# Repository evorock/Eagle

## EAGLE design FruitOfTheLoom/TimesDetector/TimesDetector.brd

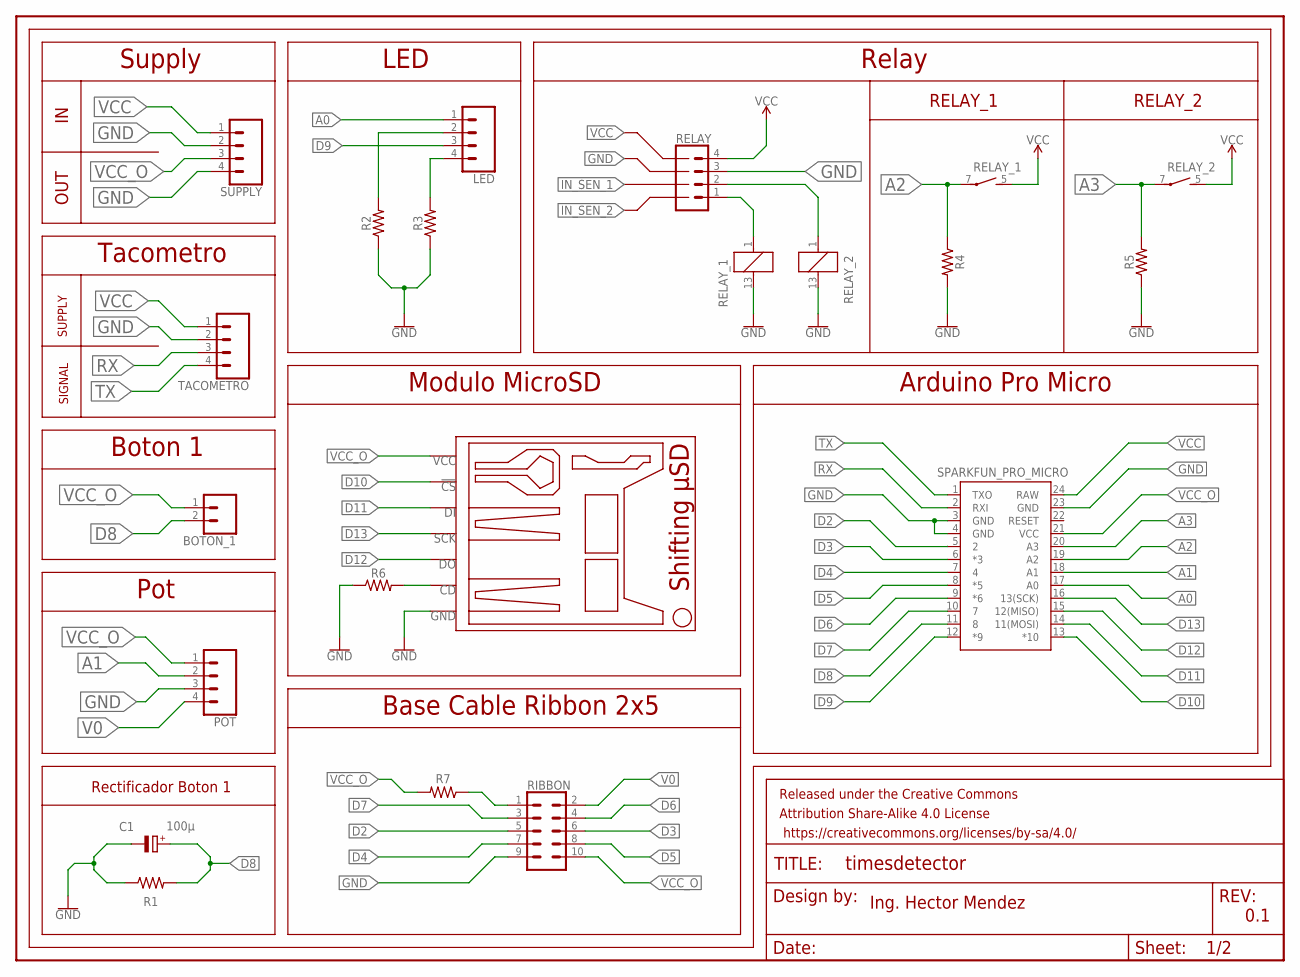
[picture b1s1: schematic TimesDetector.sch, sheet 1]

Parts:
B1: SPARKFUN_PRO_MICRO
BOTON_1: CONN_025MM; SCREWTERMINAL-5MM-2
C1: 100µ; E2,5-6E
FRAME1: FRAME-LETTER; CREATIVE_COMMONS
LED: CONN_04SCREW_LOCK; SCREWTERMINAL-3.5MM-4_LOCK
MODULE1: MICROSD_SPARKFUN_LEVEL_SHIFTING_MODULE; MICROSD_SPARKFUN_LEVEL_SHFTING_MODULE
POT: CONN_04SCREW_LOCK; SCREWTERMINAL-3.5MM-4_LOCK
R1, R2, R3, R4, R5, R6, R7: AXIAL-0.3
RELAY: CONN_04SCREW_LOCK; SCREWTERMINAL-3.5MM-4_LOCK
RELAY_1, RELAY_2: G6D-1A-ASI12VDC; G6D
RIBBON: CONN_05X2SHD; 2X5-SHROUDED
SUPPLY: CONN_04SCREW_LOCK; SCREWTERMINAL-3.5MM-4_LOCK
TACOMETRO: CONN_04SCREW_LOCK; SCREWTERMINAL-3.5MM-4_LOCK

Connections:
A0: B1.17 (A0), LED.1
A1: B1.18 (A1), POT.2
A2: B1.19 (A2), R4.P$1 (1), RELAY_1.7
A3: B1.20 (A3), R5.P$2 (2), RELAY_2.7
D2: B1.5 (2), RIBBON.5; also elsewhere on the board
D3: B1.6 (*3), RIBBON.6; also elsewhere on the board
D4: B1.7 (4), RIBBON.7
D5: B1.8 (*5), RIBBON.8; also elsewhere on the board
D6: B1.9 (*6), RIBBON.4; also elsewhere on the board
D7: B1.10 (7), RIBBON.3
D8: B1.11 (8), BOTON_1.2, C1.+, R1.P$2 (2)
D9: B1.12 (*9), LED.3; also elsewhere on the board
D10: B1.13 (*10), MODULE1.P_!CS
D11: B1.14 (11(MOSI)), MODULE1.P_DI
D12: B1.15 (12(MISO)), MODULE1.P_DO
D13: B1.16 (13(SCK)), MODULE1.P_SCK
GND: B1.3 (GND), B1.4 (GND), B1.23 (GND), C1.-, MODULE1.P_GND (GND), POT.3, R1.P$1 (1), R2.P$1 (1), R3.P$1 (1), R4.P$2 (2), R5.P$1 (1), R6.P$1 (1), RELAY.3, RELAY_1.13 (2), RELAY_2.13 (2), RIBBON.9, SUPPLY.2, SUPPLY.4, TACOMETRO.2
IN_SEN_1: RELAY.2, RELAY_2.1
IN_SEN_2: RELAY.1, RELAY_1.1
unnamed: MODULE1.P_CD, R6.P$2 (2)
unnamed: LED.4, R3.P$2 (2)
unnamed: LED.2, R2.P$2 (2)
unnamed: R7.P$1 (1), RIBBON.1
RX: B1.2 (RXI), TACOMETRO.3
TX: B1.1 (TXO), TACOMETRO.4
V0: POT.4, RIBBON.2
VCC: B1.24 (RAW), RELAY.4, RELAY_1.5 (S), RELAY_2.5 (S), SUPPLY.1, TACOMETRO.1
VCC_O: B1.21 (VCC), BOTON_1.1, MODULE1.P_VCC, POT.1, R7.P$2 (2), RIBBON.10, SUPPLY.3

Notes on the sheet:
Supply
Tacometro
Boton 1
Pot
LED
OUT
SIGNAL
SUPPLY
Rectificador Boton 1
Relay
Modulo MicroSD
Arduino Pro Micro
Base Cable Ribbon 2x5
Ing. Hector Mendez
0.1
RELAY_1
RELAY_2

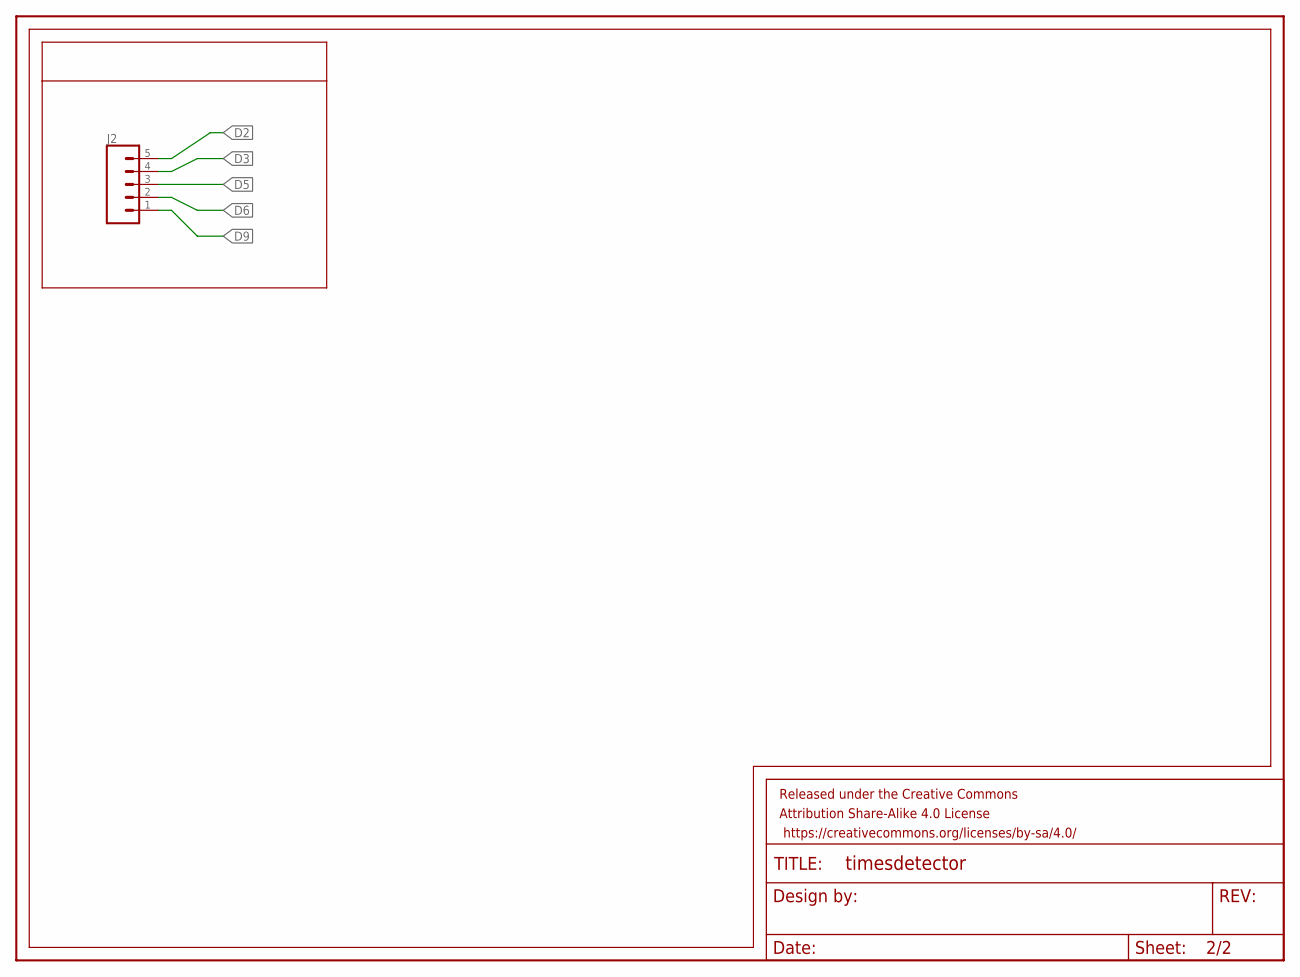
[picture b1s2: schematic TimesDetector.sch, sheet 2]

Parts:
FRAME3: FRAME-LETTERNO_PACKAGE; DUMMY
J2: CONN_05PTH_LONGPADS; 1X05_LONGPADS

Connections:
D2: J2.5; also elsewhere on the board
D3: J2.4; also elsewhere on the board
D5: J2.3; also elsewhere on the board
D6: J2.2; also elsewhere on the board
D9: J2.1; also elsewhere on the board

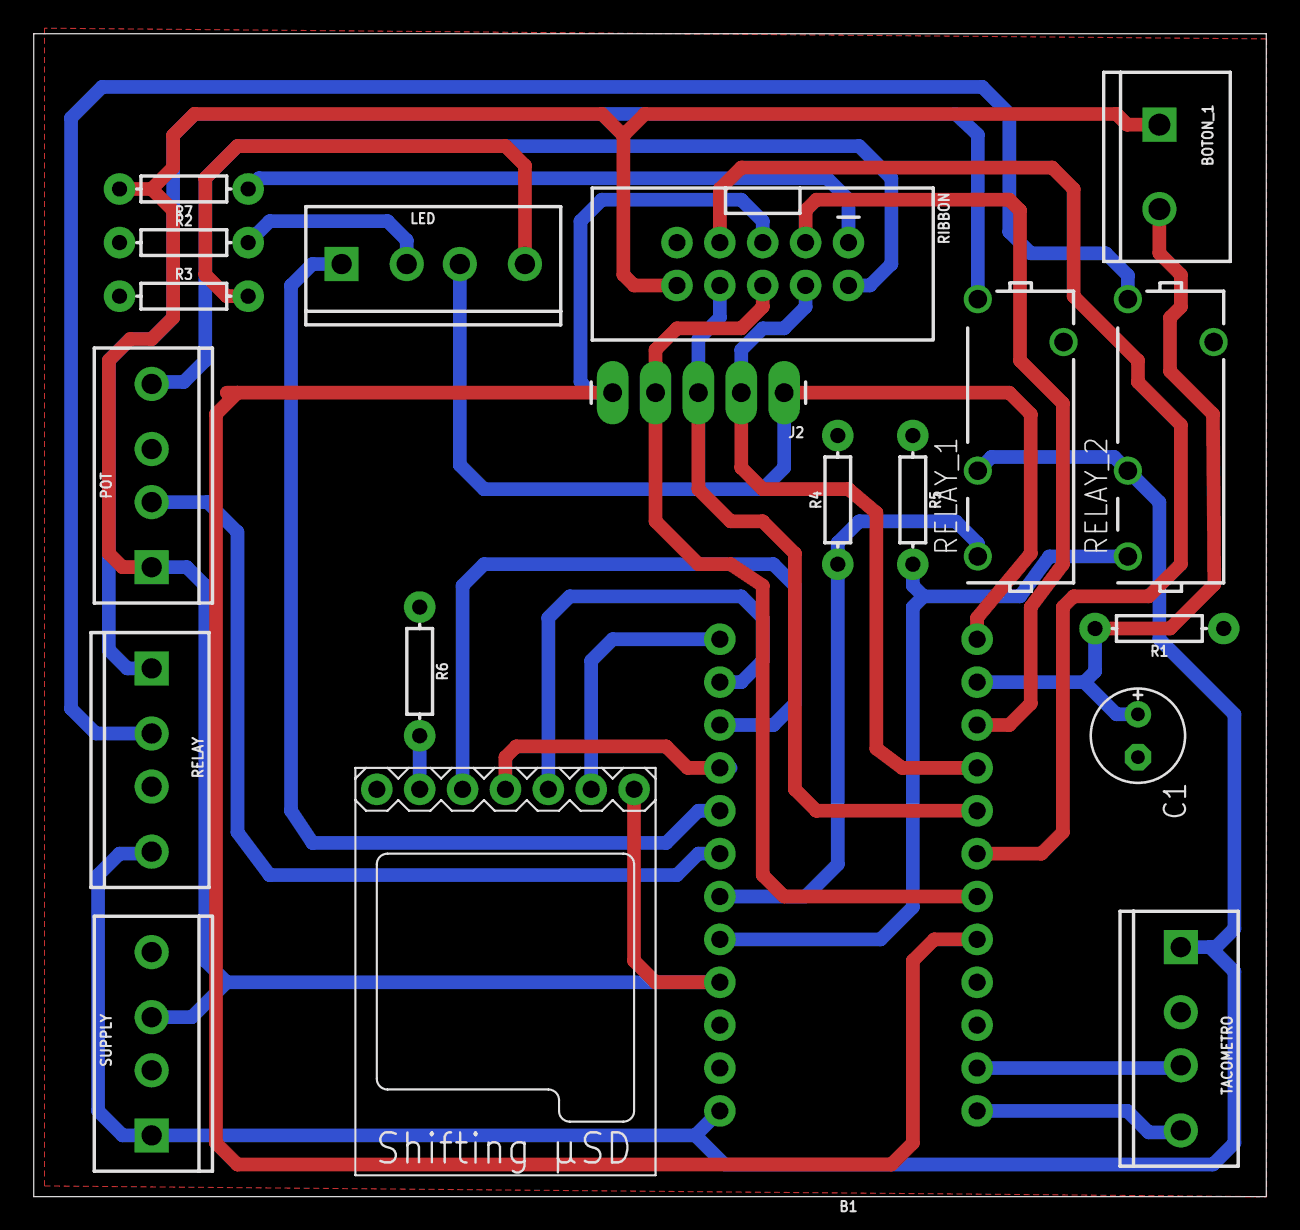
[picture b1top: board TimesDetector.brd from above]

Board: 2 copper layers, 73.0 x 68.9 mm, 22 parts (0 on the bottom side), 28 nets.

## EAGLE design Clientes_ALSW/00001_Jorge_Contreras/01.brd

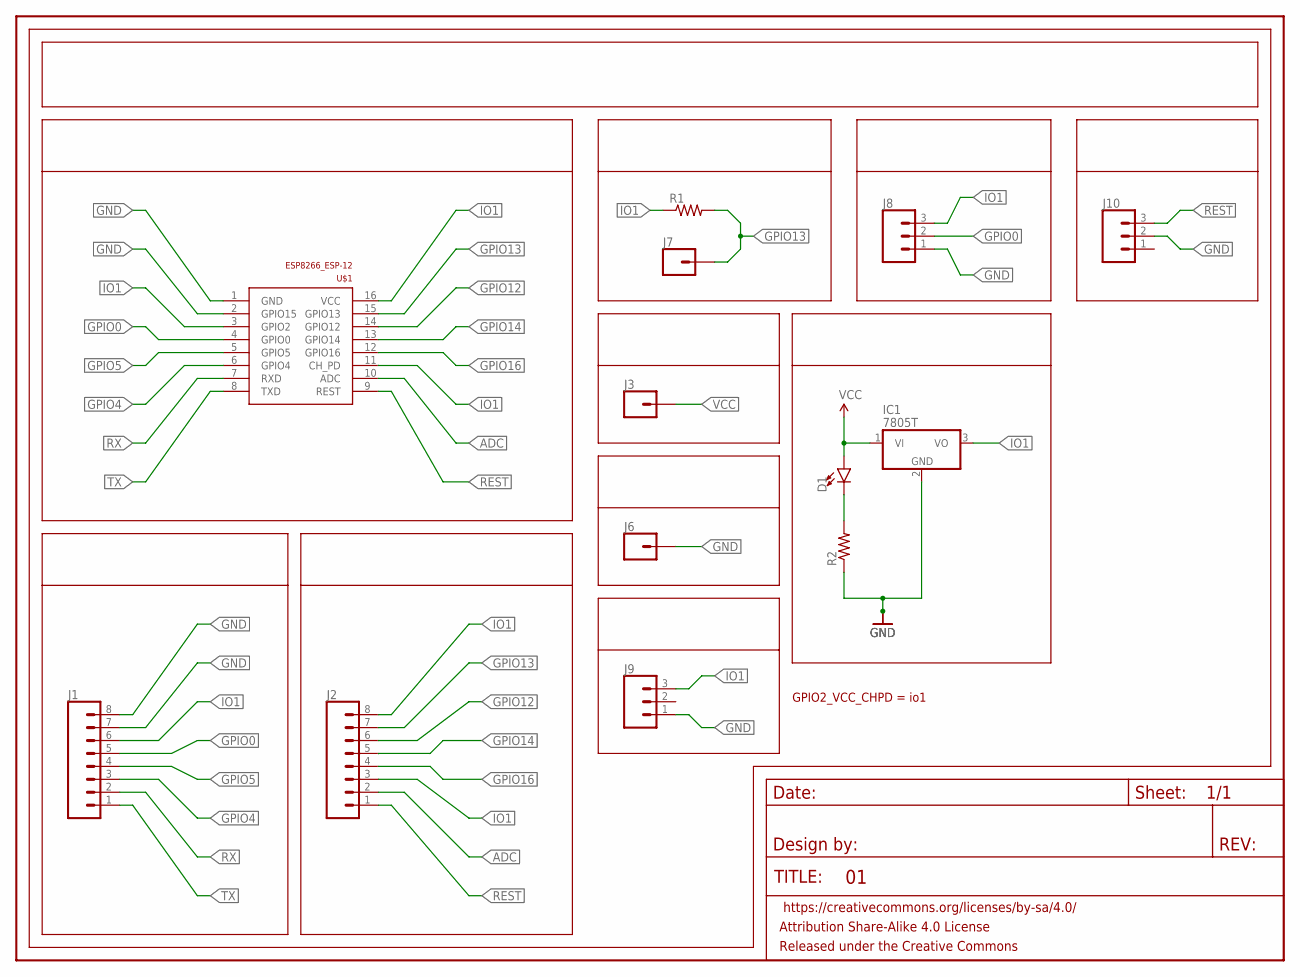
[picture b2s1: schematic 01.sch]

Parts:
D1: LED5MM; LED_5MM
FRAME1: FRAME-LETTER; CREATIVE_COMMONS
IC1: 7805T; TO220H
J1, J2: CONN_08LONGPADS; 1X08_LONGPADS
J3, J6, J7: CONN_01PTH_LONGPAD; 1X01_LONGPAD
J8, J9, J10: CONN_03LONGPADS; 1X03_LONGPADS
R1, R2: R-US_0204/7; 0204/7
U$1: ESP8266_ESP-12; ESP8266-ESP12

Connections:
ADC: J2.2, U$1.10 (ADC)
GND: IC1.2 (GND), J1.7, J1.8, J6.1, J8.1, J9.1, J10.2, R2.1, U$1.1 (GND), U$1.2 (GPIO15)
GPIO0: J1.5, J8.2, U$1.4 (GPIO0)
GPIO4: J1.3, U$1.6 (GPIO4)
GPIO5: J1.4, U$1.5 (GPIO5)
GPIO12: J2.6, U$1.14 (GPIO12)
GPIO13: J2.7, J7.1, R1.2, U$1.15 (GPIO13)
GPIO14: J2.5, U$1.13 (GPIO14)
GPIO16: J2.4, U$1.12 (GPIO16)
IO1: IC1.3 (VO), J1.6, J2.3, J2.8, J8.3, J9.3, R1.1, U$1.3 (GPIO2), U$1.11 (CH_PD), U$1.16 (VCC)
unnamed: D1.K (C), R2.2
REST: J2.1, J10.3, U$1.9 (REST)
RX: J1.2, U$1.7 (RXD)
TX: J1.1, U$1.8 (TXD)
VCC: D1.A, IC1.1 (VI), J3.1

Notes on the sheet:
GPIO2_VCC_CHPD = io1

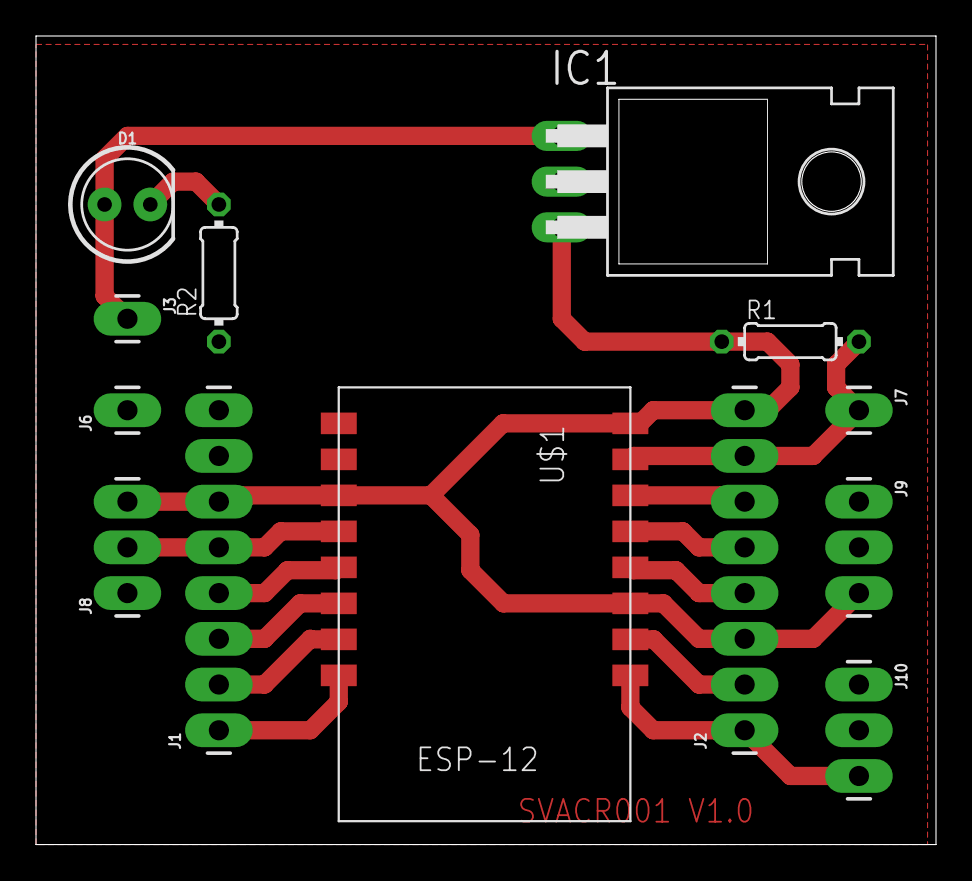
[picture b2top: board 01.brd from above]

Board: 2 copper layers, 50.0 x 44.9 mm, 14 parts (0 on the bottom side), 15 nets.

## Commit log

2018-03-19 Creacion de repositorio para Autodesk Eagle - Version Gratuita
2018-03-19 Proyector de detecto de tiempos Fruit of the Loom
2018-03-19 Ignorar archivos temporales de eagle
2018-03-19 Creacion de proyecto detector de tiempo y creacion de librerias - modulo de micro sd (solo el contorno y conexion)
2018-03-19 ordenamiento y conexion
2018-03-20 Conexiones de circuitos, relay, led, boton1
2018-03-20 Finalizacion de esquematico, erc con aprobaciones de conexion, inicializacion de placa
2018-03-21 Finalizacion de esquematico, ordenamiento de diseño de placa electronica
2018-03-21 Actualizacion de PDF
2018-03-23 Orden de los componentes segun el cliente
2018-03-25 Finalizacion de diseño de circuito, fase de revision
2018-04-02 Realizacion de proyecto clientes, agregar librerias
2018-04-03 Correcion de pistas, generacion de pdf listos para revelar PCB
2018-05-05 Correcion de carpetas, modificacion de proyecto personal

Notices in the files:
parts and their libraries:
SparkFun-LED: Licensing: Creative Commons ShareAlike 4.0 International - https://creativecommons.org/licenses/by-sa/4.0
SparkFun-Aesthetics: Released under the Creative Commons Attribution Share-Alike 4.0 License
SparkFun-Aesthetics: https://creativecommons.org/licenses/by-sa/4.0
